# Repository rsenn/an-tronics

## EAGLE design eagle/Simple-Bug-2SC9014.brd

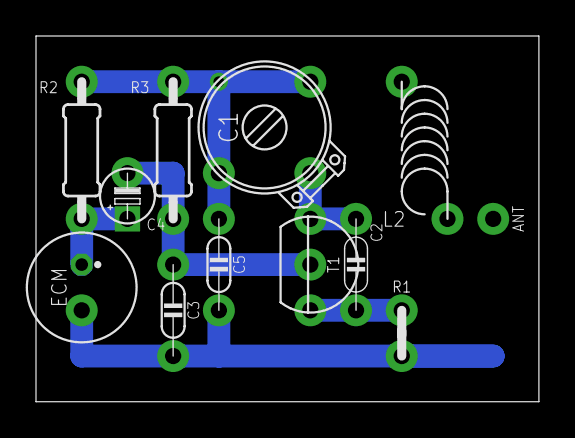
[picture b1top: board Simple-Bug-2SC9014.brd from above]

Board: 2 copper layers, 27.9 x 20.3 mm, 12 parts (0 on the bottom side), 6 nets.

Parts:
ANT: ANT; SPAD
C1: 1.6-15pF; TRIM-2222-808
C2: 4.7pF; C050-020X036
C3: 1nF; C050-020X036/V
C4: 1μF; E2,5-3/V
C5: 22nF; C050-020X036/V
ECM: ECM-4
L2: 1μH; L-04/8V
R1: 4.7Ω; 0204/2V
R2: 4.7kΩ; 0204/7-V
R3: 10kΩ; 0204/7-V
T1: 2SC9014; TO92-EBC

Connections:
+UB: C1.1, C1.3, C5.1, R2.1, R3.1
GND: C3.2, C5.2, ECM.2, R1.2
unnamed: C1.2, C2.1, T1.C
unnamed: C2.2, R1.1, T1.E
unnamed: C3.1, C4.-, R3.2, T1.B
unnamed: C4.+, ECM.1, R2.2

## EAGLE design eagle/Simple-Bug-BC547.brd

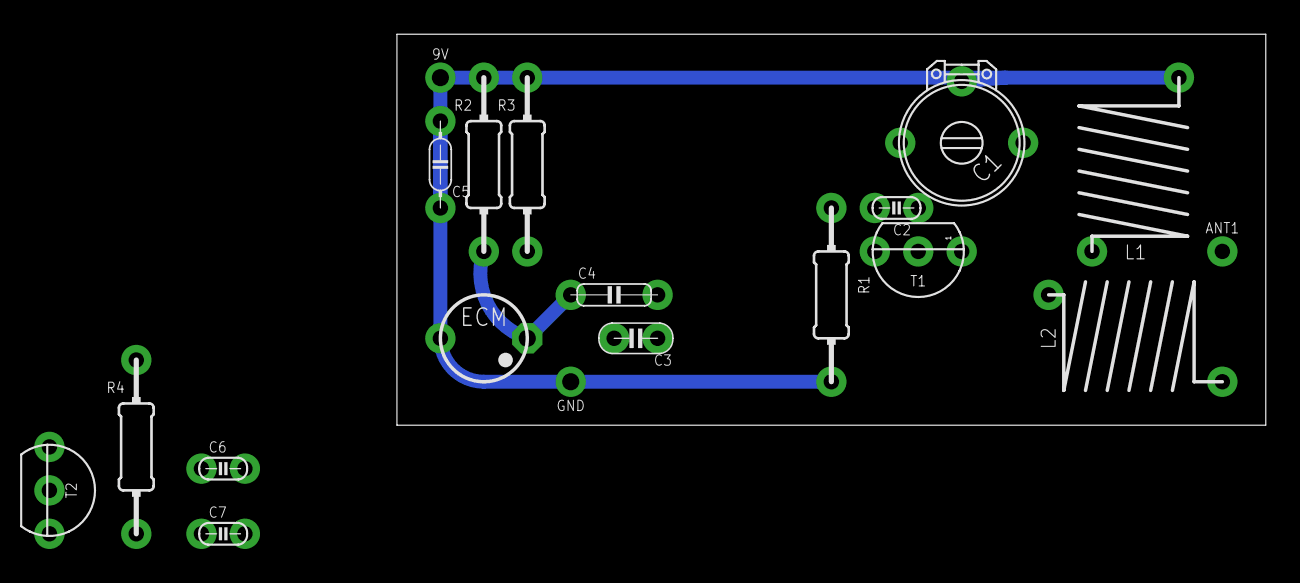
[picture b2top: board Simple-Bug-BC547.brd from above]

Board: 2 copper layers, 50.8 x 22.9 mm, 19 parts (0 on the bottom side), 8 nets.

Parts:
9V: SPAD; SPAD@1
ANT1: ANT; SPAD
C1: 3.2-45pF; TRIM-2222-808
C2, C7: 10pF; C025-015X024
C3: 1nF; C025-020X036
C4: 22nF; C050-020X044
C5: 22nF; C050-020X036/V
C6: 39pF; C025-015X024
ECM: ECM-5
GND: SPAD; SPAD@1
L1, L2: 0.1μH; L-08-10/5
R1: 470Ω; 0204/10
R2: 22kΩ; 0204/10-V
R3: 47kΩ; 0204/10-V
R4: 150kΩ; 0204/10-V
T1: BC547; TO92
T2: BF959; TO92-CEB

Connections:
+UB: 9V.1, C1.2, C5.1, C6.1, L1.2, L2.2, R2.1, R3.1, R4.1
GND: C3.2, C5.2, ECM.2, GND.1, R1.2, T2.E
unnamed: ANT1.1, L2.1, T2.C
unnamed: C1.1, C2.1, C6.2, C7.1, L1.1, T1.1
unnamed: C2.2, R1.1, T1.3
unnamed: C7.2, R4.2, T2.B
unnamed: C3.1, C4.2, R3.2, T1.2
unnamed: C4.1, ECM.1, R2.2

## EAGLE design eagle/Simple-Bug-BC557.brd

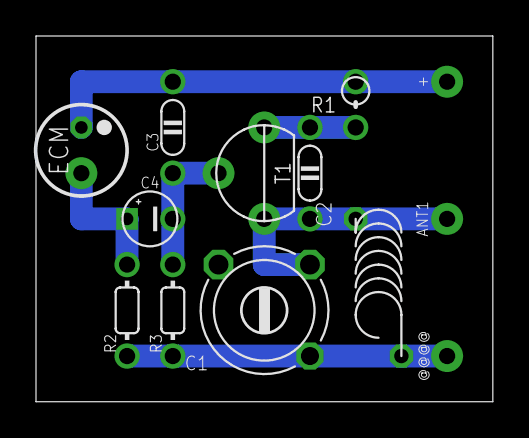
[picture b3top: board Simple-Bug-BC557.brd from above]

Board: 2 copper layers, 25.4 x 20.3 mm, 13 parts (0 on the bottom side), 6 nets.

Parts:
+: SPAD
@@@@: SPAD
ANT1: ANT; SPAD
C1: C-TR-PH20127; TRIM808-45
C2: 4.7pF; C050-020X036
C3: 1nF; C050-020X036
C4: E2,5-3
ECM: ECM-5
L1: 1μH; L-04/7
R1: 0202V
R2: 22kΩ; 0202/5
R3: 47kΩ; 0202/5
T1: BC557; TO92-CBE-A

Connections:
+UB: +.1, C3.2, ECM.1, R1.2
GND: @@@@.1, C1.3, L1.2, R2.1, R3.1
unnamed: ANT1.1, C1.2, C2.1, L1.1, T1.C
unnamed: C2.2, R1.1, T1.E
unnamed: C3.1, C4.-, R3.2, T1.B
unnamed: C4.+, ECM.2, R2.2

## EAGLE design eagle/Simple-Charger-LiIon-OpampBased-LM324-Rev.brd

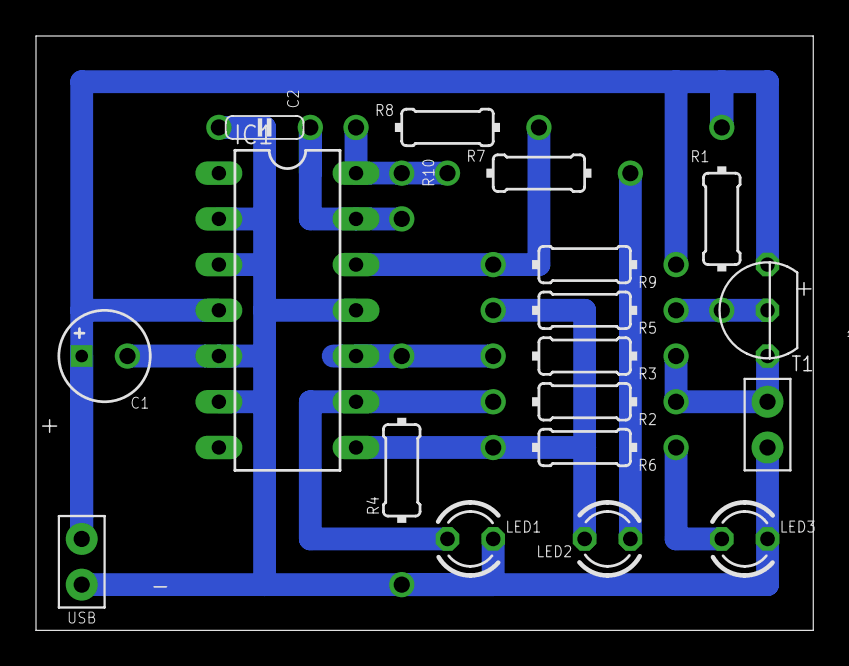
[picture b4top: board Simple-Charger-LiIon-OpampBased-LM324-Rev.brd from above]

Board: 2 copper layers, 43.2 x 33.0 mm, 19 parts (0 on the bottom side), 12 nets.

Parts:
C1: 100μF/16V; E2,5-5
C2: 100nF; C050-020X044/V
IC1: LM324N; DIL14
LED1: Red; LED_3MM
LED2: Blue; LED_3MM
LED3: Green; LED_3MM
LI-ION: SPAD+-
R1: 220Ω; 0204/10-V
R2, R6, R7: 1kΩ; 0204/10
R3: 2kΩ; 0204/10
R4: 2kΩ; 0204/12-V
R5, R8: 680Ω; 0204/10
R9: 27kΩ; 0204/10
R10: 1MΩ; 0204/2.54
T1: BC327; TO92
USB: SPAD-+

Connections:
GND: C1.-, C2.2, IC1.2, IC1.3, IC1.5, IC1.6, IC1.11, LED1.K, LED3.K, LI-ION.1, R4.2, USB.1
unnamed: IC1.12, R8.2, R9.2
unnamed: LED2.A, R7.2
unnamed: C2.1, IC1.13, R10.1
unnamed: IC1.14, R7.1, R8.1, R10.2
unnamed: IC1.9, LED1.A, R2.2
unnamed: IC1.8, LED2.K, R5.2, R6.2
unnamed: R1.2, R5.1, T1.2
unnamed: LI-ION.2, R2.1, R3.1, T1.1
unnamed: LED3.A, R6.1
unnamed: IC1.10, R3.2, R4.1
V+: C1.+, IC1.4, R1.1, R9.1, T1.3, USB.2

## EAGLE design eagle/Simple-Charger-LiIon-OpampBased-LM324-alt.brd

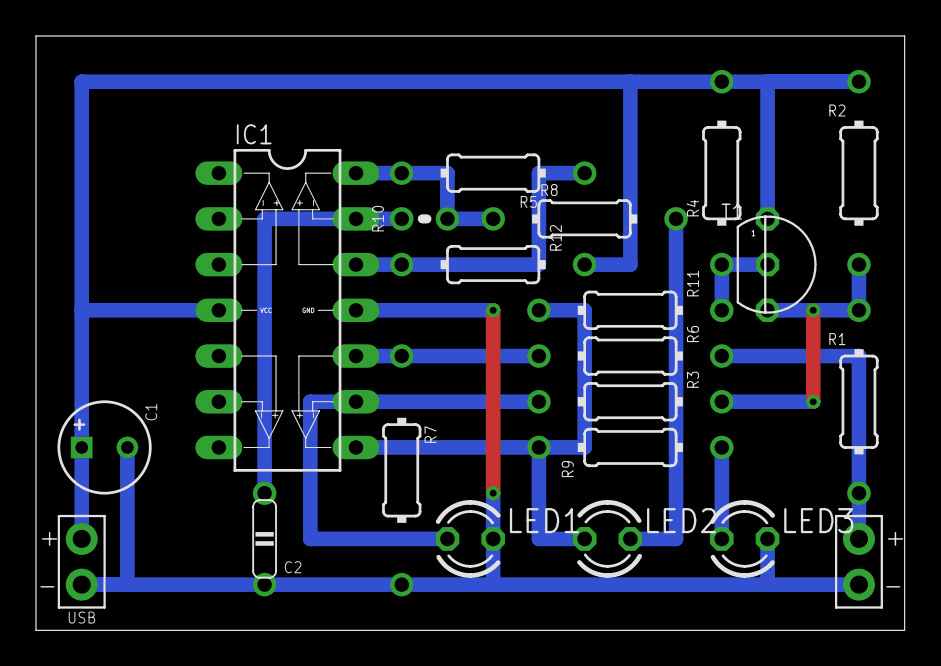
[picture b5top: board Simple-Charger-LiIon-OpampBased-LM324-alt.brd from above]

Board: 2 copper layers, 48.3 x 33.0 mm, 21 parts (0 on the bottom side), 13 nets.

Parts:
C1: 100μF/16V; E2,5-5/V
C2: 68nF; C050-020X044/V
IC1: LM324-LM324; DIL14-LM324
LED1: Green; LED3MM
LED2: Blue; LED3MM
LED3: Red; LED3MM
LI-ION: SPAD+-
R1: 1Ω; 0204/10-V
R2: 2.7kΩ; 0204/10-V
R3: 2.2kΩ; 0204/10-V
R4: 220Ω; 0204/10
R5: 470Ω; 0204/10
R6: 4.7kΩ; 0204/10-V
R7: 3.6kΩ; 0204/12-V
R8: 680Ω; 0204/10
R9: 1kΩ; 0204/10-V
R10: 680kΩ; 0204/2V
R11: 470Ω; 0204/10-V
R12: 12kΩ; 0204/10-V
T1: BC327; TO92
USB: SPAD-+

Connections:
BAT+: LI-ION.2, R1.2, R6.1
D2A: LED2.A, R8.2
D3A: LED3.A, R9.2
GND: C1.-, C2.1, IC1.11, LED1.K, LED3.K, LI-ION.1, R7.1, USB.1
unnamed: R4.1, R11.1, T1.2
unnamed: R1.1, R2.2, R3.1, T1.3
OA1+: IC1.12, R5.1, R12.2
OA1-: C2.2, IC1.13, R10.1
OA1=: IC1.14, R5.2, R8.1, R10.2
OA2+: IC1.10, R6.2, R7.2
OA2-: IC1.9, LED1.A, R3.2
OA2=: IC1.8, LED2.K, R9.1, R11.2
V+: C1.+, IC1.4, R2.1, R4.2, R12.1, T1.1, USB.2

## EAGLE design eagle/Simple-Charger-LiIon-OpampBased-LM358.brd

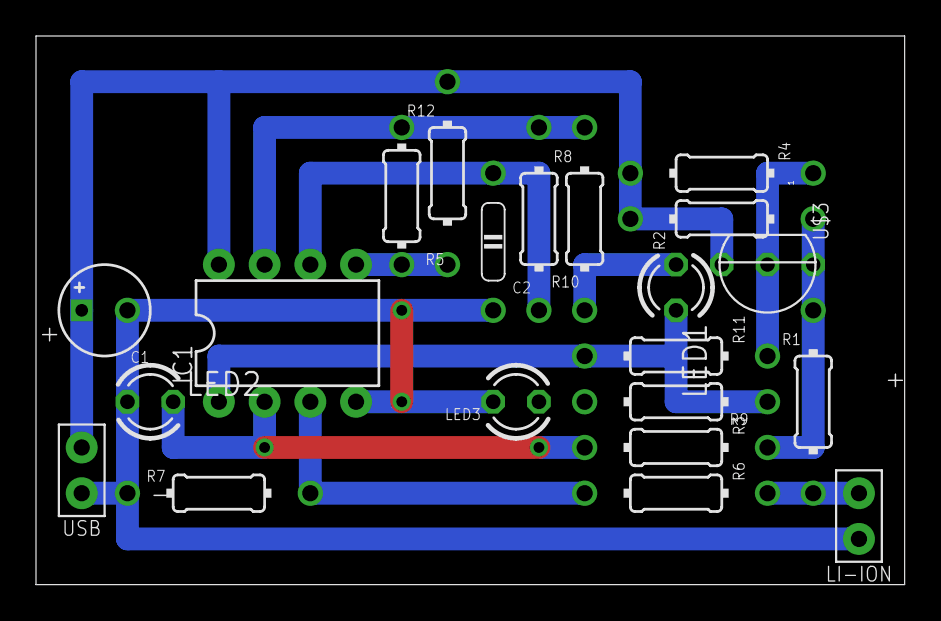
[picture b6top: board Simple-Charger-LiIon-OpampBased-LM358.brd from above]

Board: 2 copper layers, 48.3 x 30.5 mm, 21 parts (0 on the bottom side), 13 nets.

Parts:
C1: 100μF/16V; E2,5-5
C2: 68nF; C075-020X044/V
IC1: LM358N; DIL08
LED1: Red; LED3MM
LED2: Green; LED3MM
LED3: BLUE; LED_3MM
LI-ION: SPAD+-+-; SPAD+-
R1: 1Ω; 0204/10-V
R2: 2.7kΩ; 0204/10-V
R3: 2.2kΩ; 0204/10-V
R4: 220Ω; 0204/10-V
R5: 470Ω; 0204/7-V
R6: 4.7kΩ; 0204/10-V
R7: 3.6kΩ; 0204/10
R8: 680Ω; 0204/10-V
R9: 1kΩ; 0204/10
R10: 680kΩ; 0204/10-V
R11: 470Ω; 0204/10-V
R12: 12kΩ; 0204/10-V
U$3: BC327; TO92
USB: SPAD+--+; SPAD-+

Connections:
GND: C1.-, C2.1, IC1.4, LED2.A, LED3.K, LI-ION.1, R7.1, USB.1
unnamed: IC1.5, R5.1, R12.2
unnamed: IC1.7, R5.2, R8.1, R10.2
unnamed: C2.2, IC1.6, R10.1
unnamed: LED3.A, R9.2
unnamed: IC1.2, LED2.K, R3.2
unnamed: IC1.1, LED1.K, R9.1, R11.2
unnamed: LED1.A, R8.2
unnamed: R4.1, R11.1, U$3.2
unnamed: R1.1, R2.2, R3.1, U$3.1
unnamed: LI-ION.2, R1.2, R6.1
unnamed: IC1.3, R6.2, R7.2
V+: C1.+, IC1.8, R2.1, R4.2, R12.1, U$3.3, USB.2
